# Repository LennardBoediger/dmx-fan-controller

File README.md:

# DMX Fan Controller
Speed controller for two old industrial fans.

https://user-images.githubusercontent.com/11893651/213900107-9a194785-94d3-4e1d-9f15-b6ec5db4715c.mov

<br>
The final installation will use two fans, a powerful fog machine and a stroboscope to create a neat effect.<br>

## Documentation 
The Fans are powerd by three-phase alternating current and come with an 0-10V control line. The lowest possible speed setting during runtime is 1.6V but 2.6V is required to start the motors from standstill

The controller board is based on the Arduino Nano (ATmega328).<br>
For the Fan Control line a 0-5V 10Bit DAC is used. The output voltage is then amplified, so that we end up with an 0-10V 10Bit DAC.<br>
To communicate over the DMX-Bus, the board is equipped with an MAX485E RS-485 transceiver.<br>
The DMX channel can be selected using a DIP switch.<br>
Additionally there is an manual control override, which allows the fan to be set to a constant speed.<br>
Mounting holes are M3.
#### Schematic:

## Safety instructions
Please don't die when using large spinning fan blades that are powered by three-phase current.

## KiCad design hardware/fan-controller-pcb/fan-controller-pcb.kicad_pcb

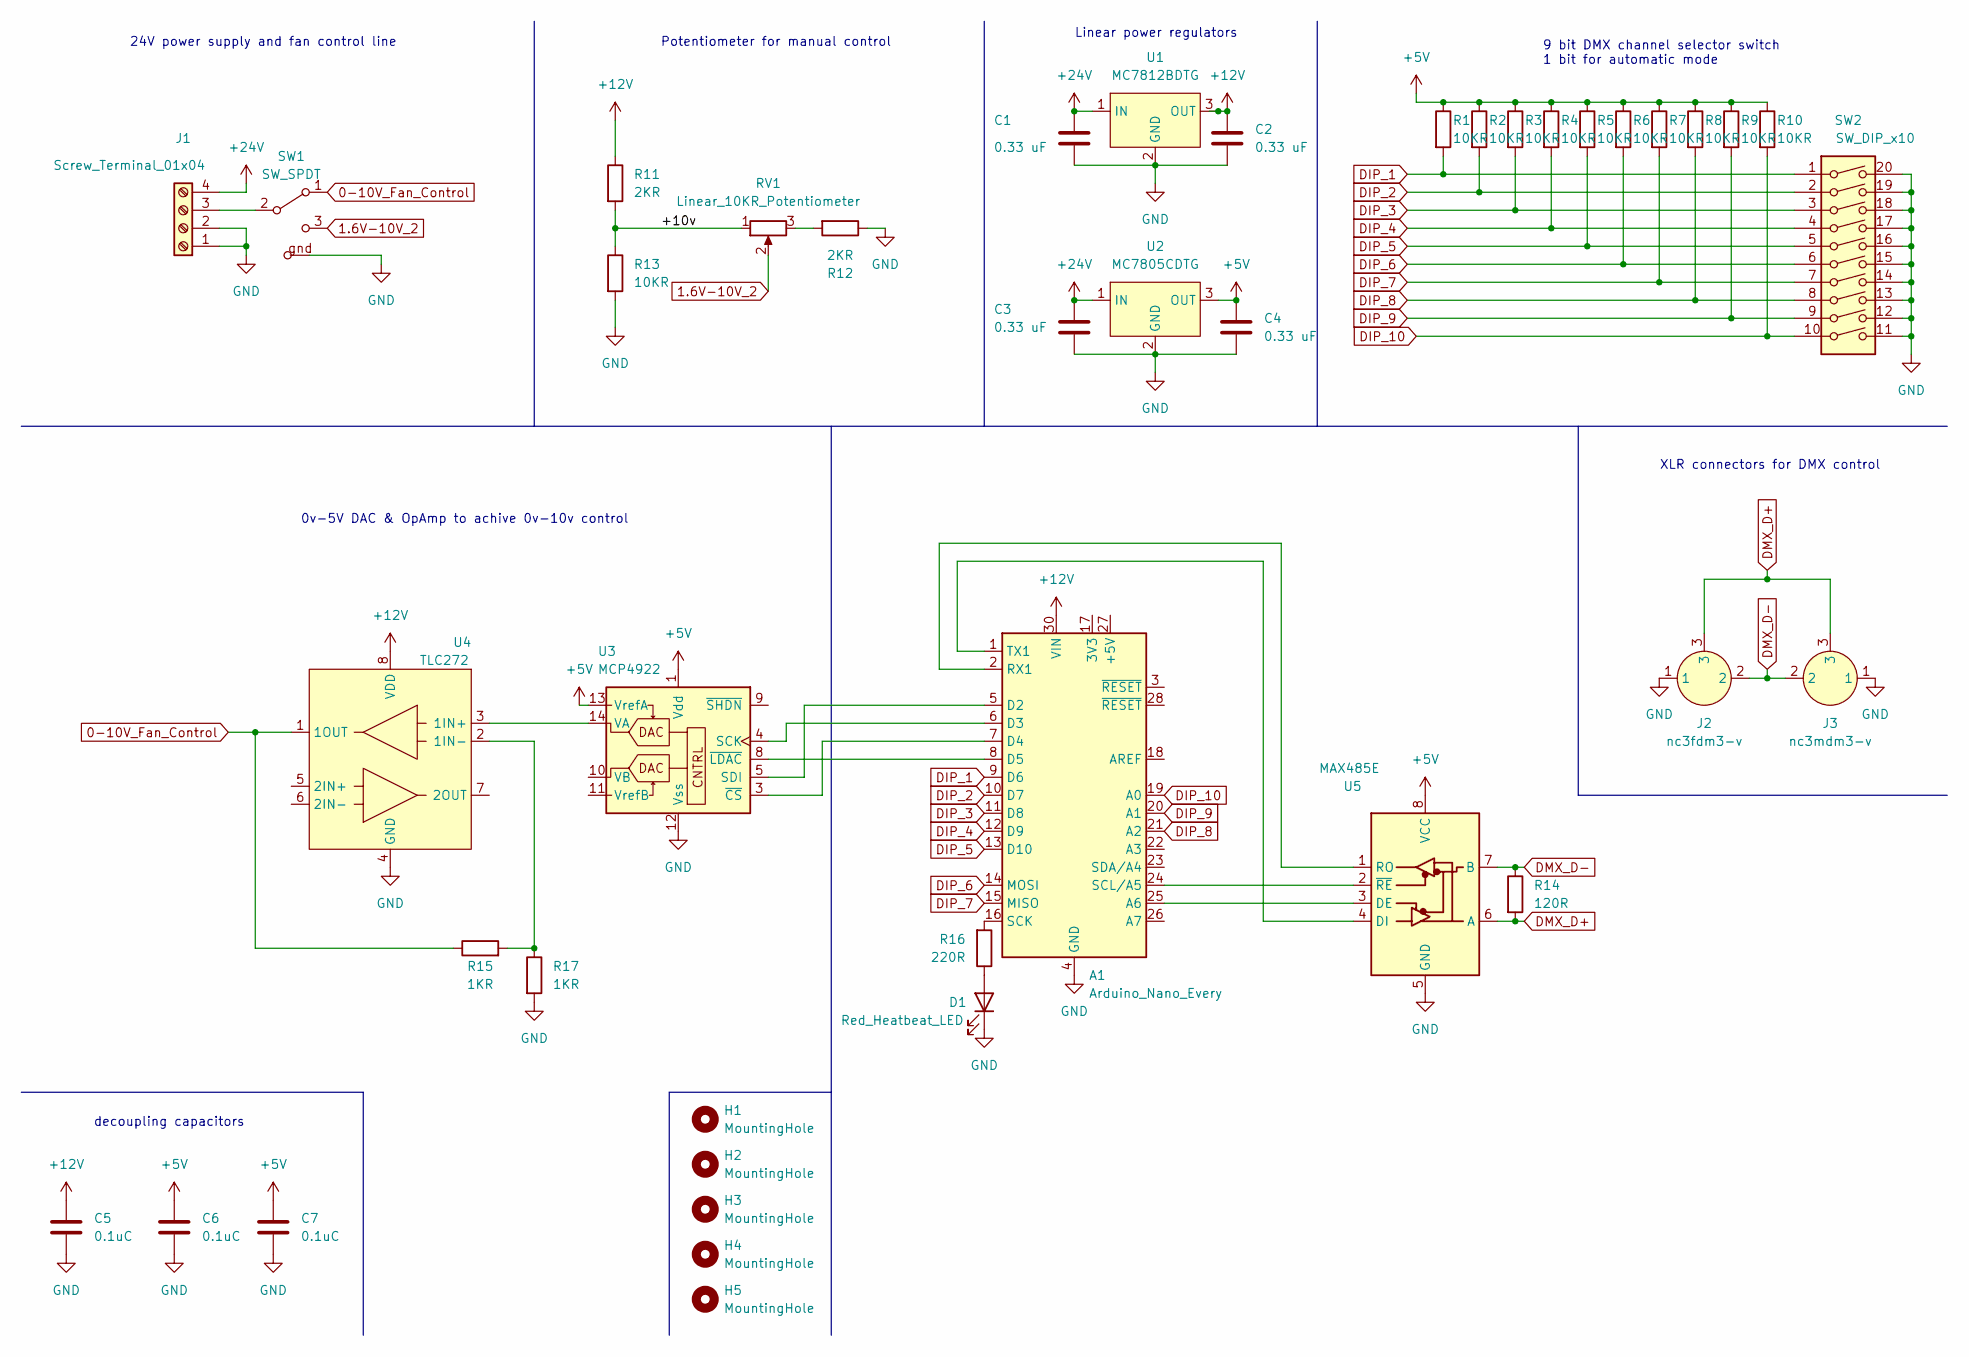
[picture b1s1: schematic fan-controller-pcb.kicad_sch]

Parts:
A1: Arduino_Nano_Every; Arduino_Nano
C1, C2, C3, C4: 0.33 uF; C_1812_4532Metric
C5, C6, C7: 0.1uC; C_0805_2012Metric
D1: Red_Heatbeat_LED; LED_D3.0mm_Horizontal_O1.27mm_Z6.0mm
H1, H2, H3, H4, H5: MountingHole; MountingHole_3.2mm_M3_ISO14580_Pad_TopBottom
J1: Screw_Terminal_01x04; TerminalBlock_Altech_AK300-4_P5.00mm
J2: nc3fdm3-v; nc3fdm3-h
J3: nc3mdm3-v; nc3mdm3-h
R1, R2, R3, R4, R5, R6, R7, R8, R9, R10, R13: 10KR; R_0603_1608Metric
R11, R12: 2KR; R_0603_1608Metric
R14: 120R; R_0603_1608Metric
R15, R17: 1KR; R_0603_1608Metric
R16: 220R; R_0603_1608Metric
RV1: Linear_10KR_Potentiometer; Potentiometer_Vishay_148-149_Single_Horizontal
SW1: SW_SPDT; WS-TOTV_6.35_Right_Angle_Toggle_Switch
SW2: SW_DIP_x10; WS-DITU_Compact_THT_Right_Angled
U1: MC7812BDTG
U2: MC7805CDTG; MC785BDTG
U3: MCP4922; MCP4912
U4: TLC272; tlc272a
U5: MAX485E

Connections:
0-10V_Fan_Control: R15.1, SW1.1 (A), U4.1 (1OUT)
1.6V-10V_2: RV1.2, SW1.3 (C)
+5V: C4.1, C6.1, C7.1, R1.1, R2.1, R3.1, R4.1, R5.1, R6.1, R7.1, R8.1, R9.1, R10.1, U2.3 (OUT), U3.1 (Vdd), U3.13 (VrefA), U5.8 (VCC)
+12V: A1.30 (VIN), C2.1, C5.1, R11.1, U1.3 (OUT), U4.8 (VDD)
+24V: C1.1, C3.1, J1.4, U1.1 (IN), U2.1 (IN)
/+10v: R11.2, R13.1, RV1.1
DIP_1: A1.9 (D6), R1.2, SW2.1
DIP_2: A1.10 (D7), R2.2, SW2.2
DIP_3: A1.11 (D8), R3.2, SW2.3
DIP_4: A1.12 (D9), R4.2, SW2.4
DIP_5: A1.13 (D10), R5.2, SW2.5
DIP_6: A1.14 (MOSI), R6.2, SW2.6
DIP_7: A1.15 (MISO), R7.2, SW2.7
DIP_8: A1.21 (A2), R8.2, SW2.8
DIP_9: A1.20 (A1), R9.2, SW2.9
DIP_10: A1.19 (A0), R10.2, SW2.10
DMX_D+: J2.3, J3.3, R14.2, U5.6 (A)
DMX_D-: J2.2, J3.2, R14.1, U5.7 (B)
GND: A1.4 (GND), A1.29 (GND), C1.2, C2.2, C3.2, C4.2, C5.2, C6.2, C7.2, D1.1 (K), J1.1, J1.2, J2.1, J3.1, R12.1, R13.2, R17.2, SW1.gnd (GND), SW2.11, SW2.12, SW2.13, SW2.14, SW2.15, SW2.16, SW2.17, SW2.18, SW2.19, SW2.20, U1.2 (GND), U2.2 (GND), U3.12 (Vss), U4.4 (GND), U5.5 (GND)
unnamed: A1.1 (TX1), U5.4 (DI)
unnamed: A1.2 (RX1), U5.1 (RO)
unnamed: A1.5 (D2), U3.5 (SDI)
unnamed: A1.6 (D3), U3.4 (SCK)
unnamed: A1.7 (D4), U3.3 (~CS)
unnamed: A1.16 (SCK), R16.2
unnamed: A1.24 (SCL/A5), U5.2 (~RE)
unnamed: A1.25 (A6), U5.3 (DE)
unnamed: D1.2 (A), R16.1
unnamed: J1.3, SW1.2 (B)
unnamed: R12.2, RV1.3
unnamed: R15.2, R17.1, U4.2 (1IN-)
unnamed: U3.14 (VA), U4.3 (1IN+)

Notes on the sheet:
24V power supply and fan control line
Potentiometer for manual control
0v-5V DAC & OpAmp to achive 0v-10v control
Linear power regulators
XLR connectors for DMX control
9 bit DMX channel selector switch 1 bit for automatic mode
decoupling capacitors

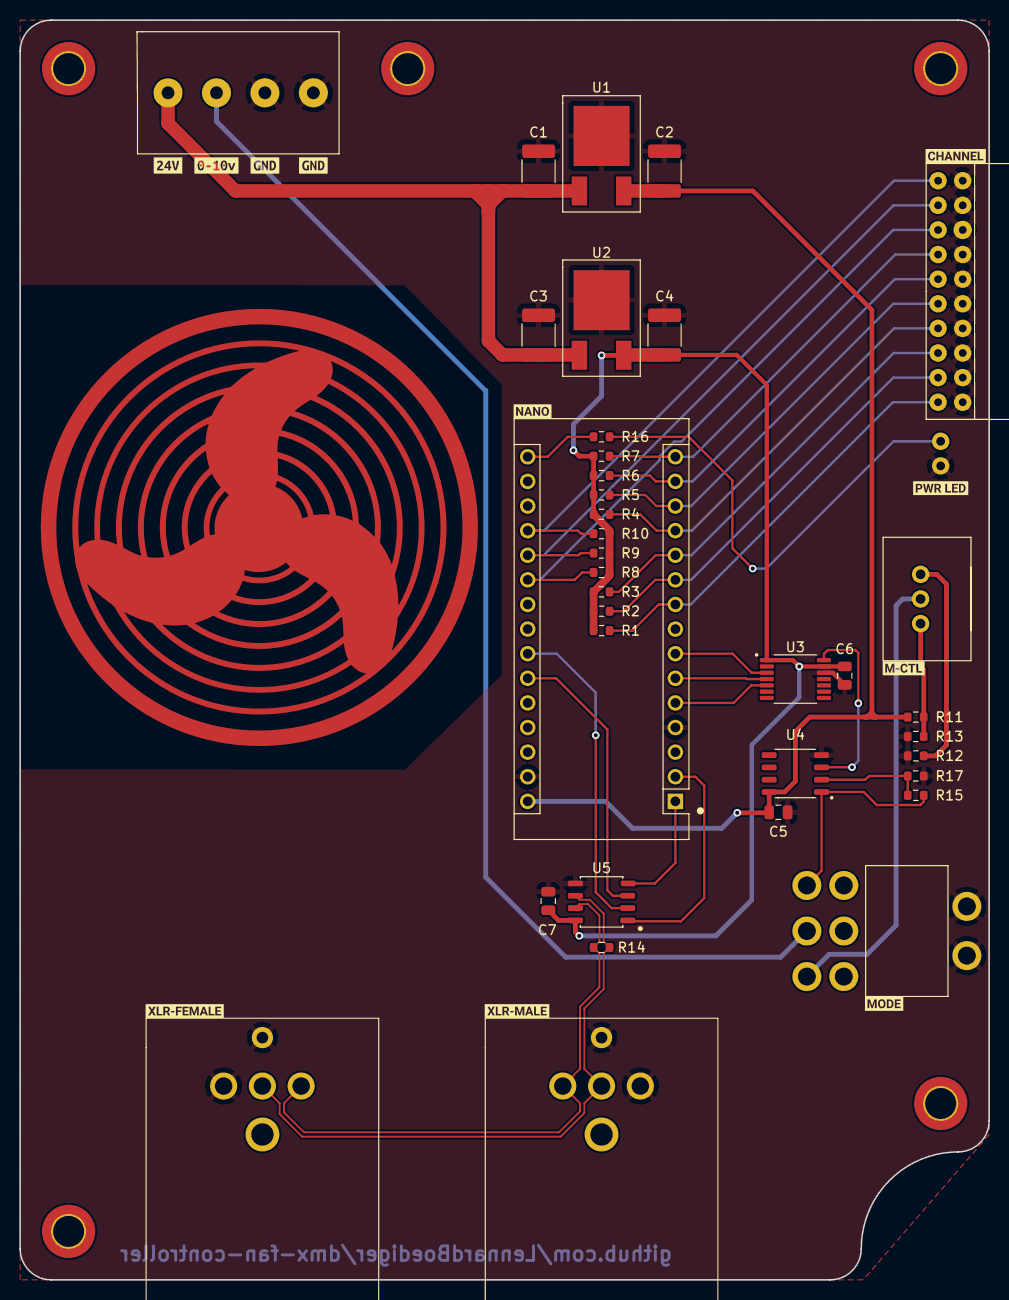
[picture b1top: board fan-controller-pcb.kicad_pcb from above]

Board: 2 copper layers, 100.0 x 130.0 mm, 53 parts (0 on the bottom side), 32 nets.

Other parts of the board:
kibuzzard-63FA74A1: G***; kibuzzard-63FA74A1
kibuzzard-63FA74BB: G***; kibuzzard-63FA74BB
kibuzzard-63FA74F3: G***; kibuzzard-63FA74F3
kibuzzard-63FA7528: G***; kibuzzard-63FA7528
kibuzzard-640DCC4D: G***; kibuzzard-640DCC4D
kibuzzard-640DCC6D: G***; kibuzzard-640DCC6D
kibuzzard-640DCC52: G***; kibuzzard-640DCC52
kibuzzard-640DCC68: G***; kibuzzard-640DCC68
kibuzzard-640DCC72: G***; kibuzzard-640DCC72
kibuzzard-640DCC79: G***; kibuzzard-640DCC79
kibuzzard-640DCC82: G***; kibuzzard-640DCC82

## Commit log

2023-01-10 add code
2023-01-10 add .DS_Store to .gitignore
2023-01-10 add basic description to README
2023-01-22 Update README.md
    Add inline Video
2023-02-15 add pcb files
2023-02-22 avoid KiCad's messiness
2023-03-13 update PCB: edge cuts, routing, symbol_lib, footprint_lib, art & data sheets
2023-03-13 update PCB: add GND-plane & PCB Name
2023-03-13 add schematic as pdf
2023-03-13 pcb rendering
2023-03-13 add Schematic as svg
2023-04-29 reorient F.Fab information
2023-04-29 add pio files to .gitignore
2023-04-29 add PIO projekt
2023-05-08 add code for basic speed control
2023-05-10 Add DMX functionality (not tested)
2023-05-10 Fix the OP-Amp circuit
2023-05-10 Fix the MCP4922 footprint and adapting the traces
2023-05-19 minor routing improvements and adding gerber files
2023-05-19 update schematic export
2023-05-19 update HW-Rev to v2
